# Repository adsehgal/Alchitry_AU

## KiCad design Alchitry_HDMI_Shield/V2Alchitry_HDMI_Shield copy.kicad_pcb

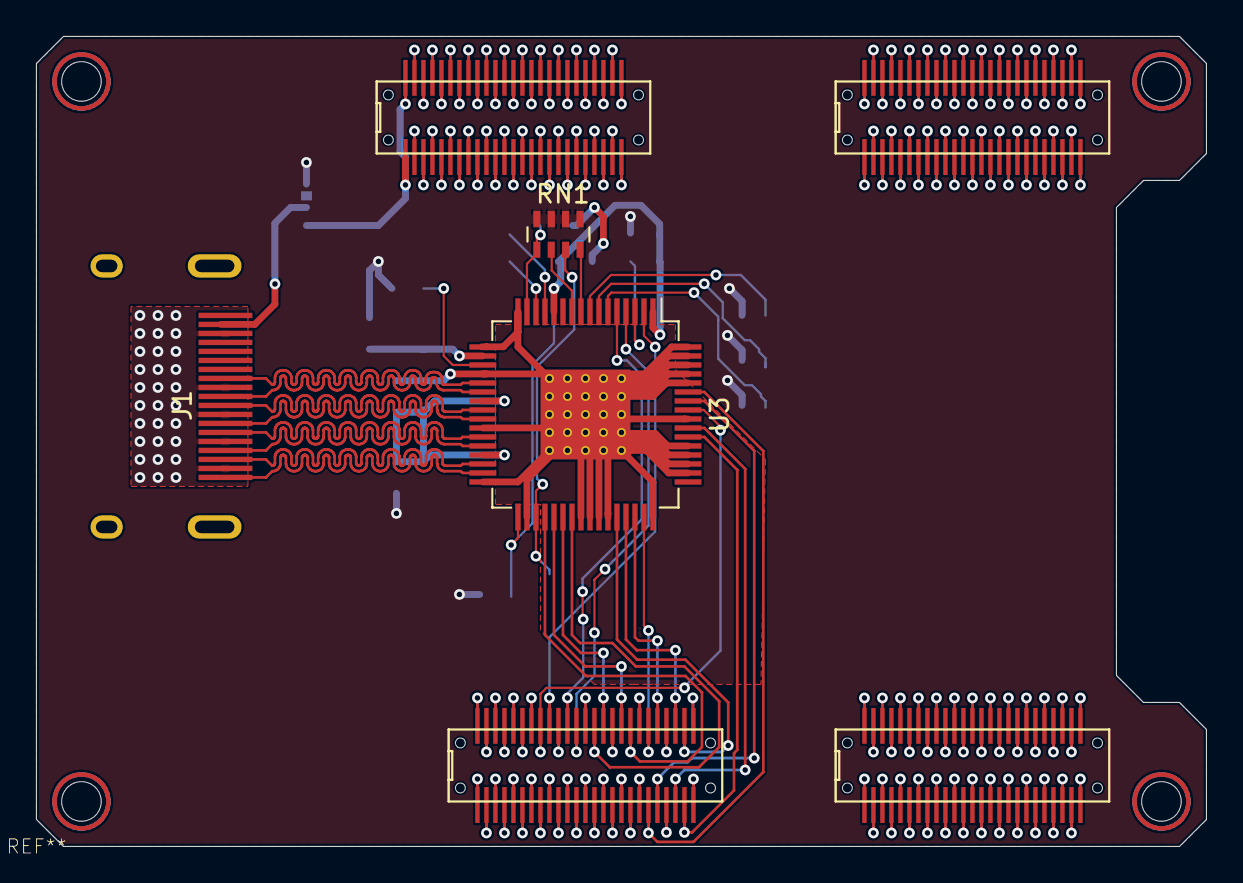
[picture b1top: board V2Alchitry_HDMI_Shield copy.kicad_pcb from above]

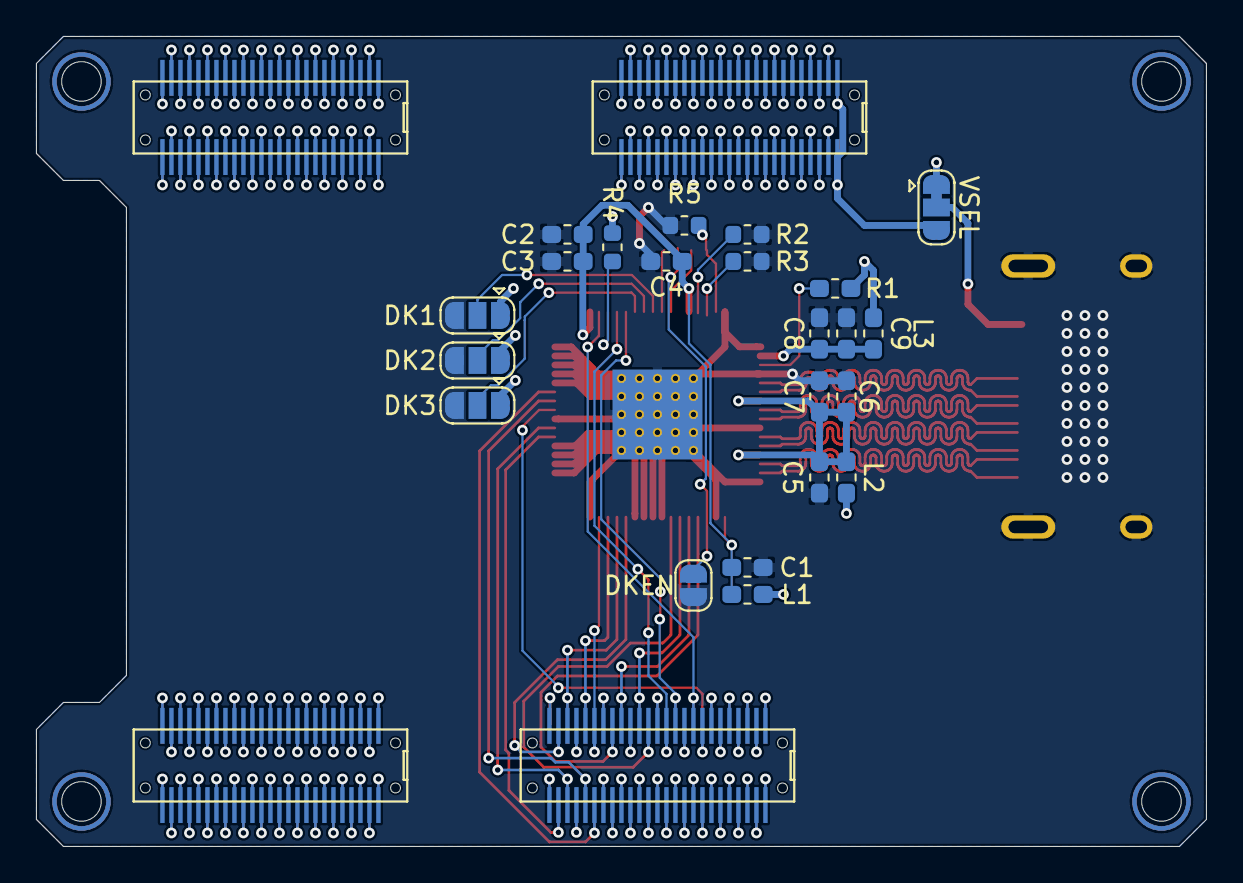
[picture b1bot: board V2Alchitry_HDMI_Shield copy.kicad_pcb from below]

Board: 2 copper layers, 65.0 x 45.0 mm, 25 parts (22 on the bottom side), 25 nets.

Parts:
C1, C2, C3, C5, C6, C8: 100nF; C_0603_1608Metric_Pad1.05x0.95mm_HandSolder
C4, C7, C9: 10µF; C_0603_1608Metric_Pad1.05x0.95mm_HandSolder
DK1: DK1; SolderJumper-3_P1.3mm_Open_RoundedPad1.0x1.5mm
DK2: DK2; SolderJumper-3_P1.3mm_Open_RoundedPad1.0x1.5mm
DK3: DK3; SolderJumper-3_P1.3mm_Open_RoundedPad1.0x1.5mm
DKEN: DKEN; SolderJumper-2_P1.3mm_Open_RoundedPad1.0x1.5mm
J1: HDMI_A_1.4; HDMI
L1, L2, L3: 600; L_0603_1608Metric_Pad1.05x0.95mm_HandSolder
R1: 510; R_0603_1608Metric_Pad1.05x0.95mm_HandSolder
R2, R3: 10K; R_0603_1608Metric
R4: 33K; R_0603_1608Metric
R5: 91K; R_0603_1608Metric
RN1: 10K; R_Array_Concave_4x0603
U3: TFP410; HTQFP-64-1EP_10x10mm_P0.5mm_EP8x8mm_Mask4.4x4.4mm_ThermalVi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
VSEL: V_Sel; SolderJumper-3_P1.3mm_Bridged12_RoundedPad1.0x1.5mm

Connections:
+3V3: DK1.1, DK2.1, DK3.1, L1.1, L2.1, L3.1, R1.1, R4.2, RN1.1, RN1.2, RN1.3, RN1.4, VSEL.1
/HDMI/CK+: J1.10, U3.22
/HDMI/CK-: J1.12, U3.21
/HDMI/D0+: J1.7, U3.25
/HDMI/D0-: J1.9, U3.24
/HDMI/D1+: J1.4, U3.28
/HDMI/D1-: J1.6, U3.27
/HDMI/D2+: J1.1, U3.31
/HDMI/D2-: J1.3, U3.30
/HDMI/DK1: DK1.2, U3.8
/HDMI/DK2: DK2.2, U3.7
/HDMI/DK3: DK3.2, U3.6
/HDMI/ISEL: R2.1, U3.13
GNDREF: C1.2, C2.2, C3.2, C4.2, C5.2, C6.2, C7.2, C8.2, C9.2, DK1.3, DK2.3, DK3.3, DKEN.1, J1.2, J1.5, J1.8, J1.11, J1.17, J1.SH, R2.2, R3.2, R5.2, U3.16, U3.17, U3.20, U3.26, U3.32, U3.34, U3.40, U3.41, U3.42, U3.43, U3.48, U3.50, U3.51, U3.52, U3.53, U3.56, U3.60, U3.61, U3.62, U3.63, U3.64, U3.65
unnamed: C1.1, C2.1, C3.1, C4.1, L1.2, U3.1, U3.12, U3.33
unnamed: C5.1, C6.1, C7.1, L2.2, U3.23, U3.29
unnamed: C8.1, C9.1, L3.2, U3.18
unnamed: J1.18, VSEL.2
unnamed: DKEN.2, RN1.7, U3.35
unnamed: R1.2, U3.19
unnamed: R3.1, U3.14
unnamed: R4.1, U3.3
unnamed: R5.1, RN1.5, U3.15
unnamed: RN1.6, U3.10
unnamed: RN1.8, U3.9

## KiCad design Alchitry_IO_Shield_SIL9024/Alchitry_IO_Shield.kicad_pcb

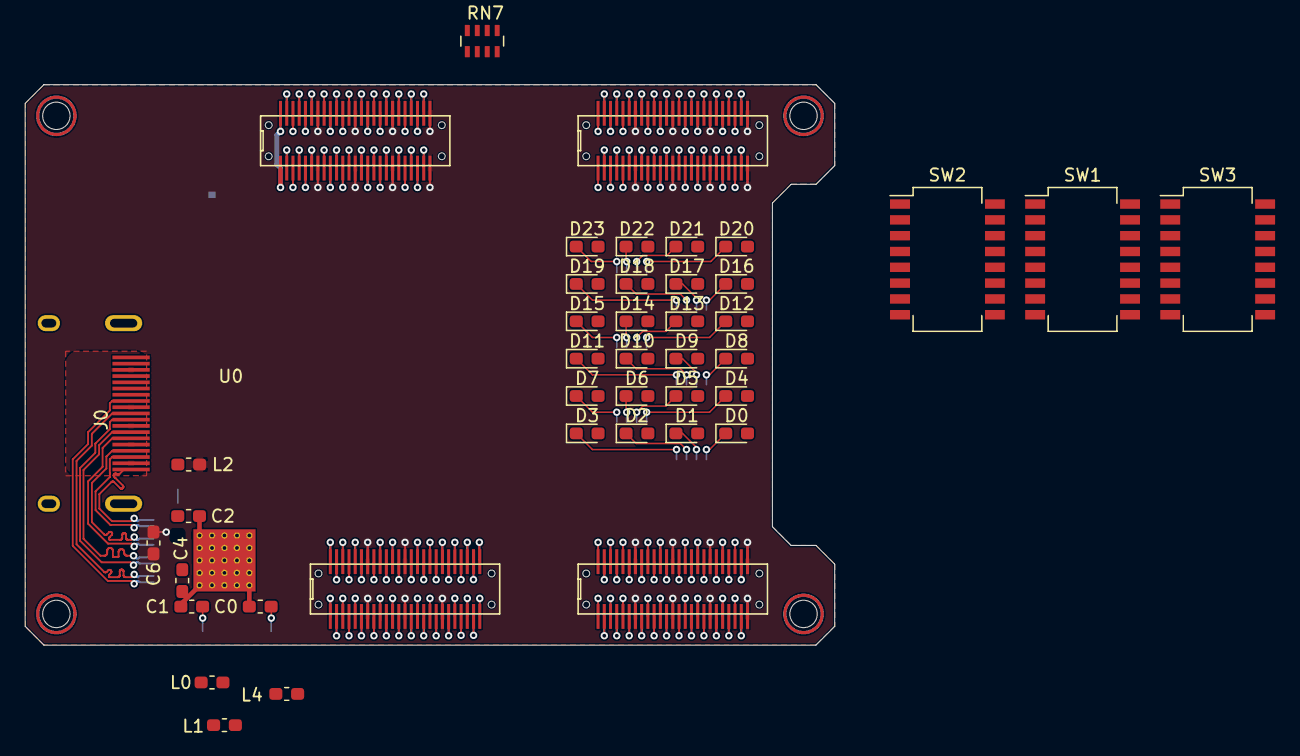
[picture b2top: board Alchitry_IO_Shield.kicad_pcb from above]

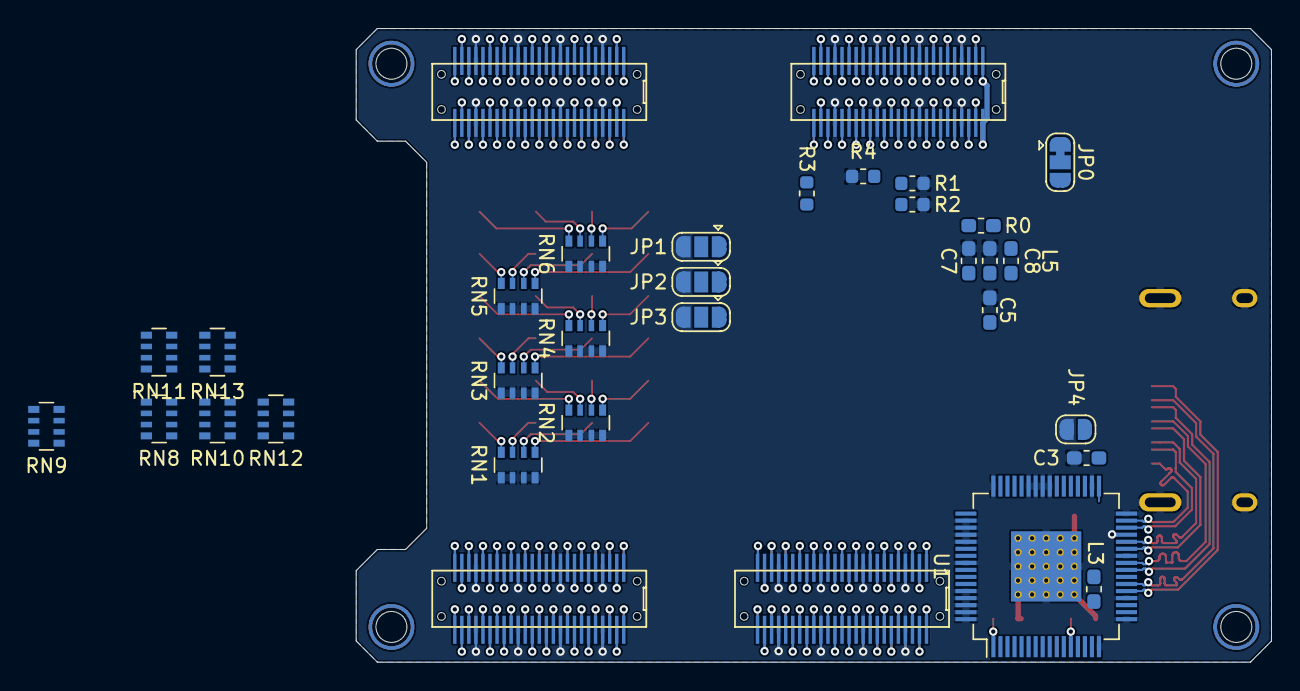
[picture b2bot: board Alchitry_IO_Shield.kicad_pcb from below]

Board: 2 copper layers, 65.0 x 45.0 mm, 68 parts (29 on the bottom side), 214 nets.

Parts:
C0, C1, C2, C4, C5, C7: 100nF; C_0603_1608Metric_Pad1.05x0.95mm_HandSolder
C3, C6, C8: 10µF; C_0603_1608Metric_Pad1.05x0.95mm_HandSolder
D0, D1, D2, D3, D4, D5, D6, D7, D8, D9, D10, D11, D12, D13, D14, D15, D16, D17, D18, D19, D20, D21, D22, D23: LED; LED_0603_1608Metric_Pad1.05x0.95mm_HandSolder
J0: HDMI_A_1.4; HDMI
JP0: V_Sel; SolderJumper-3_P1.3mm_Bridged12_RoundedPad1.0x1.5mm
JP1: DK1; SolderJumper-3_P1.3mm_Open_RoundedPad1.0x1.5mm
JP2: DK2; SolderJumper-3_P1.3mm_Open_RoundedPad1.0x1.5mm
JP3: DK3; SolderJumper-3_P1.3mm_Open_RoundedPad1.0x1.5mm
JP4: DKEN; SolderJumper-2_P1.3mm_Open_RoundedPad1.0x1.5mm
L0, L1, L2, L3, L4, L5: 600; L_0603_1608Metric_Pad1.05x0.95mm_HandSolder
R0: 510; R_0603_1608Metric_Pad1.05x0.95mm_HandSolder
R1, R2: 10K; R_0603_1608Metric
R3: 33K; R_0603_1608Metric
R4: 91K; R_0603_1608Metric
RN1, RN2, RN3, RN4, RN5, RN6, RN8, RN9, RN10, RN11, RN12, RN13: R_Pack04; R_Array_Convex_4x0603
RN7: 10K; R_Array_Concave_4x0603
SW1, SW2, SW3: SW_DIP_x08; SW_DIP_SPSTx08_Slide_Copal_CHS-08B_W7.62mm_P1.27mm
U0: boardmezzanine_new; Alchitry_Top_Bottom
U1: TFP410; HTQFP-64-1EP_10x10mm_P0.5mm_EP8x8mm_Mask4.4x4.4mm_ThermalVi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

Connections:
+3V3: JP0.1, JP1.1, JP2.1, JP3.1, L0.1, L1.1, L2.1, L3.1, L4.1, L5.1, R0.1, R3.2, RN7.1, RN7.2, RN7.3, RN7.4, U0.AB_7, U0.AB_13, U0.AB_19, U0.AB_25, U0.AB_26, U0.AB_32, U0.AB_38, U0.AB_44, U0.AT_7, U0.AT_13, U0.AT_19, U0.AT_25, U0.AT_26, U0.AT_32, U0.AT_38, U0.AT_44, U0.BB_7, U0.BB_13, U0.BB_19, U0.BB_25, U0.BB_26, U0.BB_32, U0.BB_38, U0.BB_44, U0.BT_7, U0.BT_13, U0.BT_19, U0.BT_25, U0.BT_26, U0.BT_32, U0.BT_38, U0.BT_44, U0.CB_7, U0.CB_13, U0.CB_19, U0.CB_38, U0.CB_44, U0.CT_7, U0.CT_13, U0.CT_19, U0.CT_38, U0.CT_44, U0.DB_7, U0.DB_13, U0.DB_19, U0.DB_25, U0.DB_26, U0.DB_32, U0.DB_38, U0.DB_44, U0.DT_7, U0.DT_13, U0.DT_19, U0.DT_25, U0.DT_26, U0.DT_32, U0.DT_38, U0.DT_44
+5V: JP0.3, U0.AB_1, U0.AB_50, U0.AT_1, U0.AT_50
/AN0: U0.AB_43, U0.AT_43
/AN1: U0.AB_42, U0.AT_42
/AN2: U0.AB_8, U0.AT_8
/AN3: U0.AB_9, U0.AT_9
/B0: U0.CB_20, U0.CT_20, U1.59
/B1: U0.CB_21, U0.CT_21, U1.58
/B2: U0.CB_23, U0.CT_23, U1.55
/B3: U0.CB_24, U0.CT_24, U1.54
/BTN0: U0.BB_28, U0.BT_28
/BTN1: U0.BB_27, U0.BT_27
/BTN2: U0.BB_23, U0.BT_23
/BTN3: U0.BB_24, U0.BT_24
/BTN4: U0.CB_49, U0.CT_49
/BTN5: U0.CB_48, U0.CT_48
/BTN6: U0.CB_46, U0.CT_46
/C0: U0.AB_5, U0.AT_5
/C1: U0.AB_6, U0.AT_6
/C2: U0.AB_48, U0.AT_48
/C3: U0.AB_46, U0.AT_46
/C4: U0.AB_45, U0.AT_45
/C5: U0.AB_3, U0.AT_3
/C6: U0.AB_2, U0.AT_2
/CLK: U0.CB_43, U0.CT_43, U1.57
/DE: U0.CB_42, U0.CT_42, U1.2
/DIP0: SW1.8, U0.BB_30, U0.BT_30
/DIP1: SW1.7, U0.BB_31, U0.BT_31
/DIP2: SW1.6, U0.BB_33, U0.BT_33
/DIP3: SW1.5, U0.BB_34, U0.BT_34
/DIP4: SW1.4, U0.BB_36, U0.BT_36
/DIP5: SW1.3, U0.BB_37, U0.BT_37
/DIP6: SW1.2, U0.BB_39, U0.BT_39
/DIP7: SW1.1, U0.BB_40, U0.BT_40
/DIP8: SW2.8, U0.BB_42, U0.BT_42
/DIP9: SW2.7, U0.BB_43, U0.BT_43
/DIP10: SW2.6, U0.BB_45, U0.BT_45
/DIP11: SW2.5, U0.BB_46, U0.BT_46
/DIP12: SW2.4, U0.BB_48, U0.BT_48
/DIP13: SW2.3, U0.BB_49, U0.BT_49
/DIP14: SW2.2, U0.AB_27, U0.AT_27
/DIP15: SW2.1, U0.AB_28, U0.AT_28
/DIP16: SW3.8, U0.AB_30, U0.AT_30
/DIP17: SW3.7, U0.AB_31, U0.AT_31
/DIP18: SW3.6, U0.AB_33, U0.AT_33
/DIP19: SW3.5, U0.AB_34, U0.AT_34
/DIP20: SW3.4, U0.AB_36, U0.AT_36
/DIP21: SW3.3, U0.AB_37, U0.AT_37
/DIP22: SW3.2, U0.AB_39, U0.AT_39
/DIP23: SW3.1, U0.AB_40, U0.AT_40
/DP: U0.AB_49, U0.AT_49
/G0: U0.CB_31, U0.CT_31, U1.47
/G1: U0.CB_30, U0.CT_30, U1.46
/G2: U0.CB_28, U0.CT_28, U1.45
/G3: U0.CB_27, U0.CT_27, U1.44
/HDMI/CK+: J0.10, U1.22
/HDMI/CK-: J0.12, U1.21
/HDMI/D0+: J0.7, U1.25
/HDMI/D0-: J0.9, U1.24
/HDMI/D1+: J0.4, U1.28
/HDMI/D1-: J0.6, U1.27
/HDMI/D2+: J0.1, U1.31
/HDMI/D2-: J0.3, U1.30
/HDMI/DK1: JP1.2, U1.8
/HDMI/DK2: JP2.2, U1.7
/HDMI/DK3: JP3.2, U1.6
/HDMI/ISEL: R1.1, U1.13
/HS: U0.CB_39, U0.CT_39, U1.4
/LED0: D0.2, U0.BB_21, U0.BT_21
/LED1: D1.2, U0.BB_20, U0.BT_20
/LED2: D2.2, U0.BB_18, U0.BT_18
/LED3: D3.2, U0.BB_17, U0.BT_17
/LED4: D4.2, U0.BB_15, U0.BT_15
/LED5: D5.2, U0.BB_14, U0.BT_14
/LED6: D6.2, U0.BB_12, U0.BT_12
/LED7: D7.2, U0.BB_11, U0.BT_11
/LED8: D8.2, U0.BB_9, U0.BT_9
/LED9: D9.2, U0.BB_8, U0.BT_8
/LED10: D10.2, U0.BB_6, U0.BT_6
/LED11: D11.2, U0.BB_5, U0.BT_5
/LED12: D12.2, U0.BB_3, U0.BT_3
/LED13: D13.2, U0.BB_2, U0.BT_2
/LED14: D14.2, U0.AB_24, U0.AT_24
/LED15: D15.2, U0.AB_23, U0.AT_23
/LED16: D16.2, U0.AB_21, U0.AT_21
/LED17: D17.2, U0.AB_20, U0.AT_20
/LED18: D18.2, U0.AB_18, U0.AT_18
/LED19: D19.2, U0.AB_17, U0.AT_17
/LED20: D20.2, U0.AB_15, U0.AT_15
/LED21: D21.2, U0.AB_14, U0.AT_14
/LED22: D22.2, U0.AB_12, U0.AT_12
/LED23: D23.2, U0.AB_11, U0.AT_11
/R0: U0.CB_37, U0.CT_37, U1.39
/R1: U0.CB_36, U0.CT_36, U1.38
/R2: U0.CB_34, U0.CT_34, U1.37
/R3: U0.CB_33, U0.CT_33, U1.36
/VS: U0.CB_40, U0.CT_40, U1.5
GNDREF: C0.2, C1.2, C2.2, C3.2, C4.2, C5.2, C6.2, C7.2, C8.2, J0.2, J0.5, J0.8, J0.11, J0.17, J0.SH, JP1.3, JP2.3, JP3.3, JP4.1, R1.2, R2.2, R4.2, RN1.1, RN1.2, RN1.3, RN1.4, RN2.1, RN2.2, RN2.3, RN2.4, RN3.1, RN3.2, RN3.3, RN3.4, RN4.1, RN4.2, RN4.3, RN4.4, RN5.1, RN5.2, RN5.3, RN5.4, RN6.1, RN6.2, RN6.3, RN6.4, RN8.1, RN8.2, RN8.3, RN8.4, RN9.1, RN9.2, RN9.3, RN9.4, RN10.1, RN10.2, RN10.3, RN10.4, RN11.1, RN11.2, RN11.3, RN11.4, RN12.1, RN12.2, RN12.3, RN12.4, RN13.1, RN13.2, RN13.3, RN13.4, U0.AB_4, U0.AB_10, U0.AB_16, U0.AB_22, U0.AB_29, U0.AB_35, U0.AB_41, U0.AB_47, U0.AT_4, U0.AT_10, U0.AT_16, U0.AT_22, U0.AT_29, U0.AT_35, U0.AT_41, U0.AT_47, U0.BB_4, U0.BB_10, U0.BB_16, U0.BB_22, U0.BB_29, U0.BB_35, U0.BB_41, U0.BB_47, U0.BT_4, U0.BT_10, U0.BT_16, U0.BT_22, U0.BT_29, U0.BT_35, U0.BT_41, U0.BT_47, U0.CB_4, U0.CB_10, U0.CB_16, U0.CB_22, U0.CB_29, U0.CB_35, U0.CB_41, U0.CB_47, U0.CT_4, U0.CT_10, U0.CT_16, U0.CT_22, U0.CT_29, U0.CT_35, U0.CT_41, U0.CT_47, U0.DB_4, U0.DB_10, U0.DB_16, U0.DB_22, U0.DB_29, U0.DB_35, U0.DB_41, U0.DB_47, U0.DT_4, U0.DT_10, U0.DT_16, U0.DT_22, U0.DT_29, U0.DT_35, U0.DT_41, U0.DT_47, U1.16, U1.17, U1.20, U1.26, U1.32, U1.34, U1.40, U1.41, U1.42, U1.43, U1.48, U1.50, U1.51, U1.52, U1.53, U1.56, U1.60, U1.61, U1.62, U1.63, U1.64, U1.65
unnamed: C0.1, L0.2, U1.1
unnamed: C1.1, L1.2, U1.12
unnamed: C2.1, C3.1, L2.2, U1.33
unnamed: C4.1, L3.2, U1.23
unnamed: C5.1, C6.1, L4.2, U1.29
unnamed: C7.1, C8.1, L5.2, U1.18
unnamed: D0.1, RN1.8
unnamed: D1.1, RN1.7
unnamed: D2.1, RN1.6
unnamed: D3.1, RN1.5
unnamed: D4.1, RN2.8
unnamed: D5.1, RN2.7
unnamed: D6.1, RN2.6
unnamed: D7.1, RN2.5
unnamed: D8.1, RN3.8
unnamed: D9.1, RN3.7
unnamed: D10.1, RN3.6
unnamed: D11.1, RN3.5
unnamed: D12.1, RN4.8
unnamed: D13.1, RN4.7
unnamed: D14.1, RN4.6
unnamed: D15.1, RN4.5
unnamed: D16.1, RN5.8
unnamed: D17.1, RN5.7
unnamed: D18.1, RN5.6
unnamed: D19.1, RN5.5
unnamed: D20.1, RN6.8
unnamed: D21.1, RN6.7
unnamed: D22.1, RN6.6
unnamed: D23.1, RN6.5
unnamed: J0.18, JP0.2
unnamed: JP4.2, RN7.7, U1.35
unnamed: R0.2, U1.19
unnamed: R2.1, U1.14
unnamed: R3.1, U1.3
unnamed: R4.1, RN7.5, U1.15
unnamed: RN7.6, U1.10
unnamed: RN7.8, U1.9
unnamed: RN8.5, SW1.12
unnamed: RN8.6, SW1.11
unnamed: RN8.7, SW1.10
unnamed: RN8.8, SW1.9
unnamed: RN9.5, SW1.16
unnamed: RN9.6, SW1.15
unnamed: RN9.7, SW1.14
unnamed: RN9.8, SW1.13
unnamed: RN10.5, SW2.12
unnamed: RN10.6, SW2.11
unnamed: RN10.7, SW2.10
unnamed: RN10.8, SW2.9
unnamed: RN11.5, SW2.16
unnamed: RN11.6, SW2.15
unnamed: RN11.7, SW2.14
unnamed: RN11.8, SW2.13
unnamed: RN12.5, SW3.12
unnamed: RN12.6, SW3.11
unnamed: RN12.7, SW3.10
unnamed: RN12.8, SW3.9
unnamed: RN13.5, SW3.16
unnamed: RN13.6, SW3.15
unnamed: RN13.7, SW3.14
unnamed: RN13.8, SW3.13
unnamed: U0.BB_1, U0.BT_1
unnamed: U0.BB_50, U0.BT_50
unnamed: U0.CB_1, U0.CT_1
unnamed: U0.CB_2, U0.CT_2
unnamed: U0.CB_3, U0.CT_3
unnamed: U0.CB_5, U0.CT_5
unnamed: U0.CB_6, U0.CT_6
unnamed: U0.CB_8, U0.CT_8
unnamed: U0.CB_9, U0.CT_9
unnamed: U0.CB_11, U0.CT_11
unnamed: U0.CB_12, U0.CT_12
unnamed: U0.CB_14, U0.CT_14
unnamed: U0.CB_15, U0.CT_15
unnamed: U0.CB_17, U0.CT_17
unnamed: U0.CB_18, U0.CT_18
unnamed: U0.CB_25, U0.CT_25
unnamed: U0.CB_26, U0.CT_26
unnamed: U0.CB_32, U0.CT_32
unnamed: U0.CB_45, U0.CT_45
unnamed: U0.CB_50, U0.CT_50
unnamed: U0.DB_1, U0.DT_1
unnamed: U0.DB_2, U0.DT_2
unnamed: U0.DB_3, U0.DT_3
unnamed: U0.DB_5, U0.DT_5
unnamed: U0.DB_6, U0.DT_6
unnamed: U0.DB_8, U0.DT_8
unnamed: U0.DB_9, U0.DT_9
unnamed: U0.DB_11, U0.DT_11
unnamed: U0.DB_12, U0.DT_12
unnamed: U0.DB_14, U0.DT_14
unnamed: U0.DB_15, U0.DT_15
unnamed: U0.DB_17, U0.DT_17
unnamed: U0.DB_18, U0.DT_18
unnamed: U0.DB_20, U0.DT_20
unnamed: U0.DB_21, U0.DT_21
unnamed: U0.DB_23, U0.DT_23
unnamed: U0.DB_24, U0.DT_24
unnamed: U0.DB_27, U0.DT_27
unnamed: U0.DB_28, U0.DT_28
unnamed: U0.DB_30, U0.DT_30
unnamed: U0.DB_31, U0.DT_31
unnamed: U0.DB_33, U0.DT_33
unnamed: U0.DB_34, U0.DT_34
unnamed: U0.DB_36, U0.DT_36
unnamed: U0.DB_37, U0.DT_37
unnamed: U0.DB_39, U0.DT_39
unnamed: U0.DB_40, U0.DT_40
unnamed: U0.DB_42, U0.DT_42
unnamed: U0.DB_43, U0.DT_43
unnamed: U0.DB_45, U0.DT_45
unnamed: U0.DB_46, U0.DT_46
unnamed: U0.DB_48, U0.DT_48
unnamed: U0.DB_49, U0.DT_49
unnamed: U0.DB_50, U0.DT_50

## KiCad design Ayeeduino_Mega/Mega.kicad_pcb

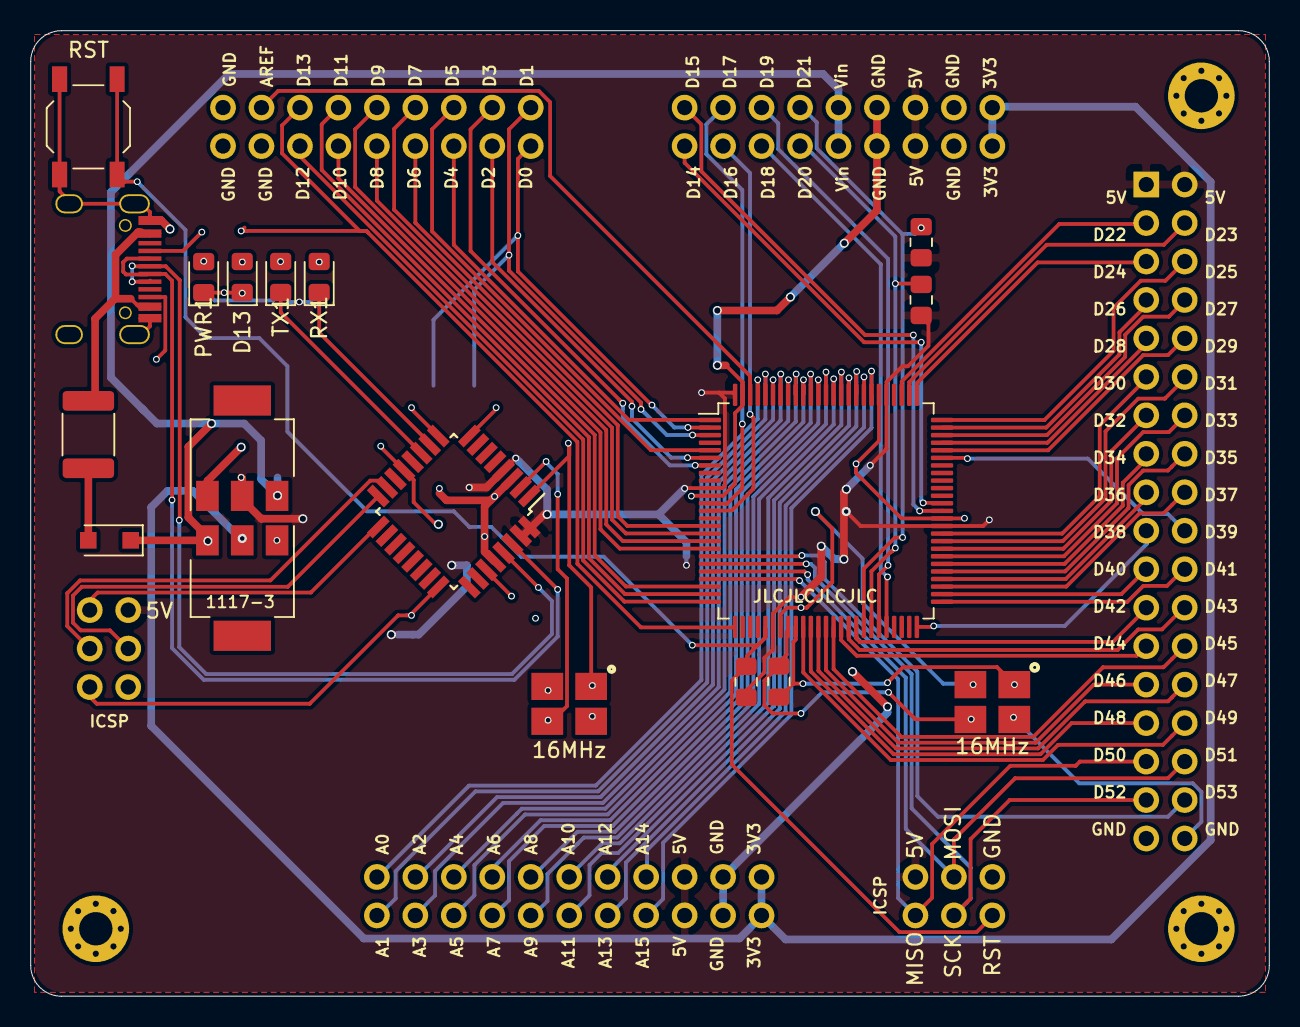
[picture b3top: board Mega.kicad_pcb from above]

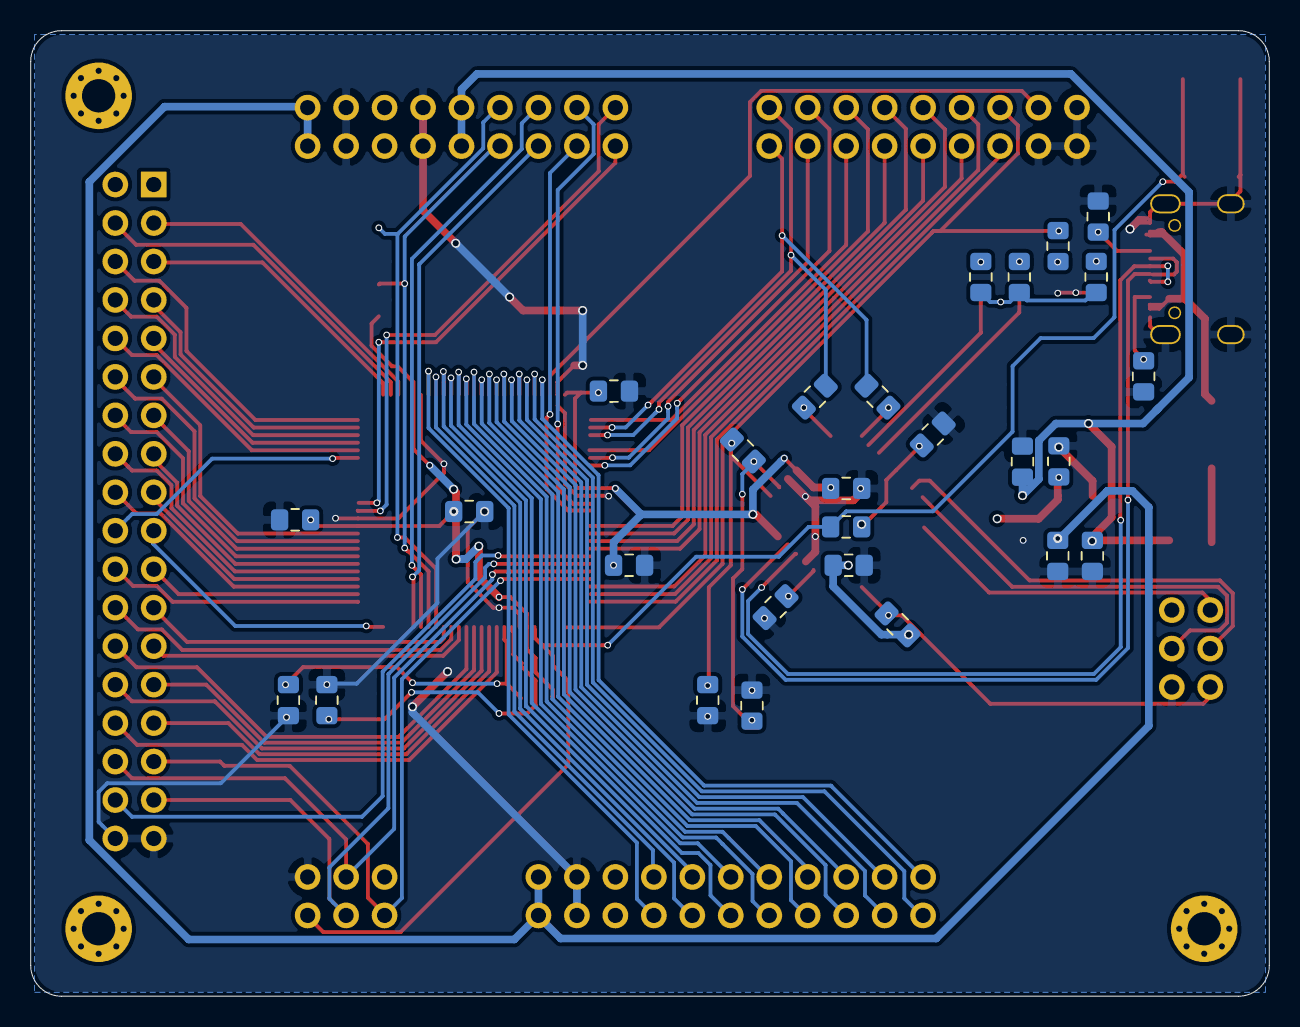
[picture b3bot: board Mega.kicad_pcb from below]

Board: 2 copper layers, 81.8 x 63.8 mm, 54 parts (27 on the bottom side), 100 nets.

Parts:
C1, C2, C3, C4, C5, C6, C12, C13, C14, C15, C16: 100nF; C_0805_2012Metric_Pad1.15x1.40mm_HandSolder
C7, C8, C9, C10: 22pF; C_0805_2012Metric_Pad1.15x1.40mm_HandSolder
C11: 1µF; C_0805_2012Metric_Pad1.15x1.40mm_HandSolder
D1: D; D_SOD-123F
D13: LED; LED_0805_2012Metric_Pad1.15x1.40mm_HandSolder
F1: Fuse; Fuse_1812_4532Metric_Pad1.30x3.40mm_HandSolder
H1, H3, H4: MountingHole; MountingHole_2.2mm_M2_Pad_Via
J1: D14-21 [COMMS]; PinHeader_2x09_P2.54mm_Vertical
J2: D22-53[SERIAL]; PinHeader_2x18_P2.54mm_Vertical
J3: D0-13 [~PWM]; PinHeader_2x09_P2.54mm_Vertical
J4, J6: ICSP; PinHeader_2x03_P2.54mm_Vertical
J5: A0-15; PinHeader_2x11_P2.54mm_Vertical
P1: USB_C_Plug; USB C C167321
PWR1: LED; LED_0805_2012Metric_Pad1.15x1.40mm_HandSolder
R1, R3, R6, R7, R8, R9: 1KΩ; R_0805_2012Metric_Pad1.15x1.40mm_HandSolder
R2, R5: 1MΩ; R_0805_2012Metric_Pad1.15x1.40mm_HandSolder
R4: 10KΩ; R_0805_2012Metric_Pad1.15x1.40mm_HandSolder
R10, R11: 5.1KΩ; R_0805_2012Metric_Pad1.15x1.40mm_HandSolder
R12, R13, R14: R_Small_US; R_0805_2012Metric_Pad1.15x1.40mm_HandSolder
R15: 330Ω; R_0805_2012Metric_Pad1.15x1.40mm_HandSolder
RX1: LED; LED_0805_2012Metric_Pad1.15x1.40mm_HandSolder
SW1: RST; SW_SPST_TL3342
TX1: LED; LED_0805_2012Metric_Pad1.15x1.40mm_HandSolder
U1: 1115-5; SOT-223
U2: 1117-3; SOT-223
U3: ATmega16U2-AU; TQFP-32_7x7mm_P0.8mm
U4: ATmega2560-16AU; TQFP-100_14x14mm_P0.5mm
Y1, Y2: 16MHz; Crystal_SMD_3225-4Pin_3.2x2.5mm_HandSoldering

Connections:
+3V3: C4.2, J1.9, J1.10, J5.21, J5.22, U2.2
+5V: C2.2, C5.2, C6.2, C13.2, C14.2, C15.2, C16.2, J1.7, J1.12, J2.1, J2.2, J4.2, J5.17, J5.18, J6.2, R1.2, R4.2, R7.2, R8.2, R12.1, R14.1, R15.1, U1.2, U3.4, U3.31, U3.32, U4.10, U4.31, U4.61, U4.80, U4.100
+VSW: C1.1, C3.1, D1.1, J1.5, J1.14, U1.3, U2.3
/D+: P1.A6, P1.B6, U3.29
/D-: P1.A7, P1.B7, U3.30
/MISO_1: J6.1, U3.17
/MOSI_1: J6.4, U3.16
/RST_1: J6.5, R4.1, U3.24
/SCK_1: J6.3, U3.15
A0: J5.2, U4.97
A1: J5.1, U4.96
A2: J5.4, U4.95
A3: J5.3, U4.94
A4: J5.6, U4.93
A5: J5.5, U4.92
A6: J5.8, U4.91
A7: J5.7, U4.90
A8: J5.10, U4.89
A9: J5.9, U4.88
A10: J5.12, U4.87
A11: J5.11, U4.86
A12: J5.14, U4.85
A13: J5.13, U4.84
A14: J5.16, U4.83
A15: J5.15, U4.82
AREF: J3.8, U4.98
D0: J3.18, R3.1, U4.2
D1: J3.1, R6.1, U4.3
D2: J3.17, U4.6
D3: J3.2, U4.7
D4: J3.16, U4.1
D5: J3.3, U4.5
D6: J3.15, U4.15
D7: J3.4, U4.16
D8: J3.14, U4.17
D9: J3.5, U4.18
D10: J3.13, U4.23
D11: J3.6, U4.24
D12: J3.12, U4.25
D13: J3.7, R13.1, U4.26
D14: J1.1, U4.64
D15: J1.18, U4.63
D16: J1.2, U4.13
D17: J1.17, U4.12
D18: J1.3, U4.46
D19: J1.16, U4.45
D20: J1.4, R8.1, U4.44
D21: J1.15, R7.1, U4.43
D22: J2.3, U4.78
D23: J2.4, U4.77
D24: J2.5, U4.76
D25: J2.6, U4.75
D26: J2.7, U4.74
D27: J2.8, U4.73
D28: J2.9, U4.72
D29: J2.10, U4.71
D30: J2.11, U4.60
D31: J2.12, U4.59
D32: J2.13, U4.58
D33: J2.14, U4.57
D34: J2.15, U4.56
D35: J2.16, U4.55
D36: J2.17, U4.54
D37: J2.18, U4.53
D38: J2.19, U4.50
D39: J2.20, U4.70
D40: J2.21, U4.52
D41: J2.22, U4.51
D42: J2.23, U4.42
D43: J2.24, U4.41
D44: J2.25, U4.40
D45: J2.26, U4.39
D46: J2.27, U4.38
D47: J2.28, U4.37
D48: J2.29, U4.36
D49: J2.30, U4.35
D50_MISO: J2.31, J4.1, U4.22
D51_MOSI: J2.32, J4.4, U4.21
D52_SCK: J2.33, J4.3, U4.20
D53_SS: J2.34, U4.19
GNDREF: C1.2, C2.1, C3.2, C4.1, C5.1, C6.1, C7.2, C8.2, C9.2, C10.2, C11.1, C13.1, C14.1, C15.1, C16.1, D13.1, J1.6, J1.8, J1.11, J1.13, J2.35, J2.36, J3.9, J3.10, J3.11, J4.6, J5.19, J5.20, J6.6, P1.A1, P1.A12, P1.B1, P1.B12, P1.S1, PWR1.1, R9.1, R10.1, R11.1, SW1.2, U1.1, U2.1, U3.3, U3.28, U4.11, U4.32, U4.62, U4.81, U4.99, Y1.2, Y1.4, Y2.2, Y2.4
unnamed: C7.1, R5.2, U3.1, Y2.1
unnamed: C8.1, R5.1, U3.2, Y2.3
unnamed: C9.1, R2.2, U4.34, Y1.1
unnamed: C10.1, R2.1, U4.33, Y1.3
unnamed: C11.2, U3.27
unnamed: C12.2, R9.2, U3.13
unnamed: D1.2, F1.2
unnamed: D13.2, R13.2
unnamed: F1.1, P1.A4, P1.A9, P1.B4, P1.B9
unnamed: P1.A5, R10.2
unnamed: P1.B5, R11.2
unnamed: PWR1.2, R12.2
unnamed: R14.2, TX1.2
unnamed: R15.2, RX1.2
RST: C12.1, J4.5, R1.1, SW1.1, U4.30
RX: R3.2, U3.9
RXL: RX1.1, U3.10
TX: R6.2, U3.8
TXL: TX1.1, U3.11

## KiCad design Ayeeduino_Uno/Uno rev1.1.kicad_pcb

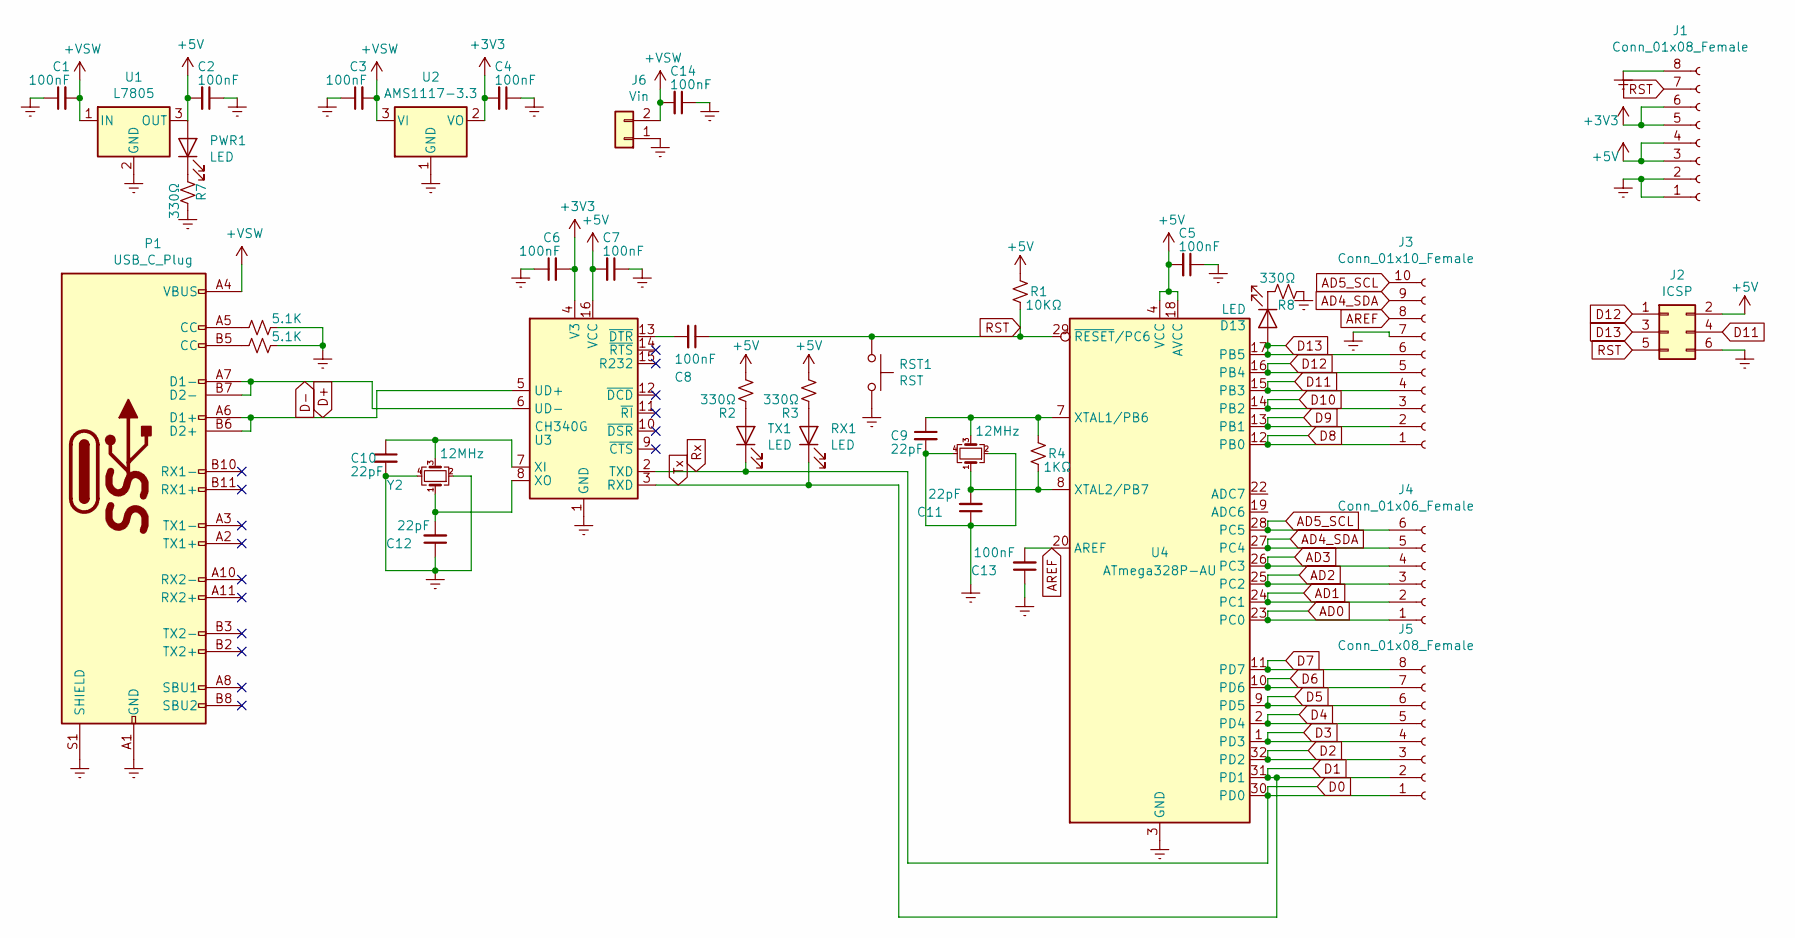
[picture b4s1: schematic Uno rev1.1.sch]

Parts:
C1, C2, C3, C4, C5, C6, C7, C8, C13, C14: 100nF; C_0805_2012Metric_Pad1.15x1.40mm_HandSolder
C9, C10, C11, C12: 22pF; C_0805_2012Metric_Pad1.15x1.40mm_HandSolder
D13: LED; LED_0805_2012Metric_Pad1.15x1.40mm_HandSolder
J1, J5: Conn_01x08_Female; PinHeader_1x08_P2.54mm_Vertical
J2: ICSP; PinHeader_2x03_P2.54mm_Vertical
J3: Conn_01x10_Female; PinHeader_1x10_P2.54mm_Vertical
J4: Conn_01x06_Female; PinHeader_1x06_P2.54mm_Vertical
J6: Vin; PinSocket_1x02_P2.54mm_Vertical
P1: USB_C_Plug; USB C C167321
PWR1: LED; LED_0805_2012Metric_Pad1.15x1.40mm_HandSolder
R1: 10KΩ; R_0805_2012Metric_Pad1.15x1.40mm_HandSolder
R2, R3, R7, R8: 330Ω; R_0805_2012Metric_Pad1.15x1.40mm_HandSolder
R4: 1KΩ; R_0805_2012Metric_Pad1.15x1.40mm_HandSolder
R5, R6: 5.1K; R_0805_2012Metric_Pad1.15x1.40mm_HandSolder
RST1: RST; SW_SPST_TL3342
RX1: LED; LED_0805_2012Metric_Pad1.15x1.40mm_HandSolder
TX1: LED; LED_0805_2012Metric_Pad1.15x1.40mm_HandSolder
U1: L7805; SOT-89-3_Handsoldering
U2: AMS1117-3.3; SOT-223-3_TabPin2
U3: CH340G; SOIC-16_3.9x9.9mm_P1.27mm
U4: ATmega328P-AU; TQFP-32_7x7mm_P0.8mm
Y1, Y2: 12MHz; Crystal_SMD_3225-4Pin_3.2x2.5mm_HandSoldering

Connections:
+3V3: C4.2, C6.2, J1.5, J1.6, U2.2 (VO), U3.4 (V3)
+5V: C2.2, C5.2, C7.2, J1.3, J1.4, J2.2, PWR1.2 (A), R1.1, R2.2, R3.2, U1.3 (OUT), U3.16 (VCC), U4.4 (VCC), U4.6 (VCC), U4.18 (AVCC)
+VSW: C1.2, C3.2, C14.2, J6.2, P1.A4 (VBUS), P1.A9 (VBUS), P1.B4 (VBUS), P1.B9 (VBUS), U1.1 (IN), U2.3 (VI)
AD0: J4.1, U4.23 (PC0)
AD1: J4.2, U4.24 (PC1)
AD2: J4.3, U4.25 (PC2)
AD3: J4.4, U4.26 (PC3)
AD4_SDA: J3.9, J4.5, U4.27 (PC4)
AD5_SCL: J3.10, J4.6, U4.28 (PC5)
AREF: C13.2, J3.8, U4.20 (AREF)
D0: J5.1, TX1.1 (K), U3.2 (TXD), U4.30 (PD0)
D1: J5.2, RX1.1 (K), U3.3 (RXD), U4.31 (PD1)
D2: J5.3, U4.32 (PD2)
D3: J5.4, U4.1 (PD3)
D4: J5.5, U4.2 (PD4)
D5: J5.6, U4.9 (PD5)
D6: J5.7, U4.10 (PD6)
D7: J5.8, U4.11 (PD7)
D8: J3.1, U4.12 (PB0)
D9: J3.2, U4.13 (PB1)
D10: J3.3, U4.14 (PB2)
D11: J2.4, J3.4, U4.15 (PB3)
D12: J2.1, J3.5, U4.16 (PB4)
D13: D13.2 (A), J2.3, J3.6, U4.17 (PB5)
D+: P1.A6 (D1+), P1.B6 (D2+), U3.5 (UD+)
D-: P1.A7 (D1-), P1.B7 (D2-), U3.6 (UD-)
GNDREF: C1.1, C2.1, C3.1, C4.1, C5.1, C6.1, C7.1, C9.2, C10.2, C11.1, C12.1, C13.1, C14.1, J1.1, J1.2, J1.8, J2.6, J3.7, J6.1, P1.A1 (GND), P1.A12 (GND), P1.B1 (GND), P1.B12 (GND), P1.S1 (SHIELD), R5.1, R6.1, R7.2, R8.1, RST1.2, U1.2 (GND), U2.1 (GND), U3.1 (GND), U4.3 (GND), U4.5 (GND), U4.21 (GND), Y1.2, Y1.4, Y2.2, Y2.4; also elsewhere on the board
unnamed: C8.2, U3.13 (~DTR)
unnamed 28: C9.1, R4.1, U4.7 (XTAL1/PB6), Y1.3; also elsewhere on the board
unnamed: C10.1, U3.7 (XI), Y2.3
unnamed 30: C11.2, R4.2, U4.8 (XTAL2/PB7), Y1.1; also elsewhere on the board
unnamed: C12.2, U3.8 (XO), Y2.1
unnamed: D13.1 (K), R8.2
unnamed: P1.A5 (CC), R5.2
unnamed: P1.B5 (CC), R6.2
unnamed: PWR1.1 (K), R7.1
unnamed: R2.1, TX1.2 (A)
unnamed: R3.1, RX1.2 (A)
RST: C8.1, J1.7, J2.5, R1.2, RST1.1, U4.29 (~RESET~/PC6)

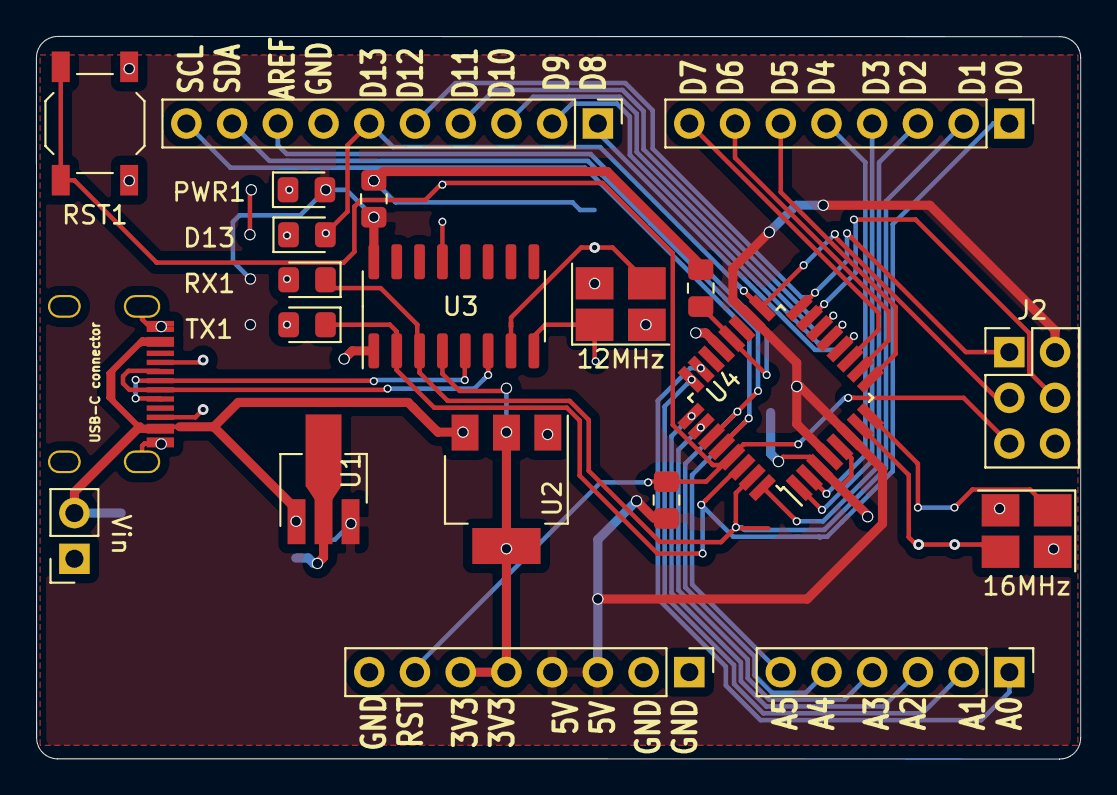
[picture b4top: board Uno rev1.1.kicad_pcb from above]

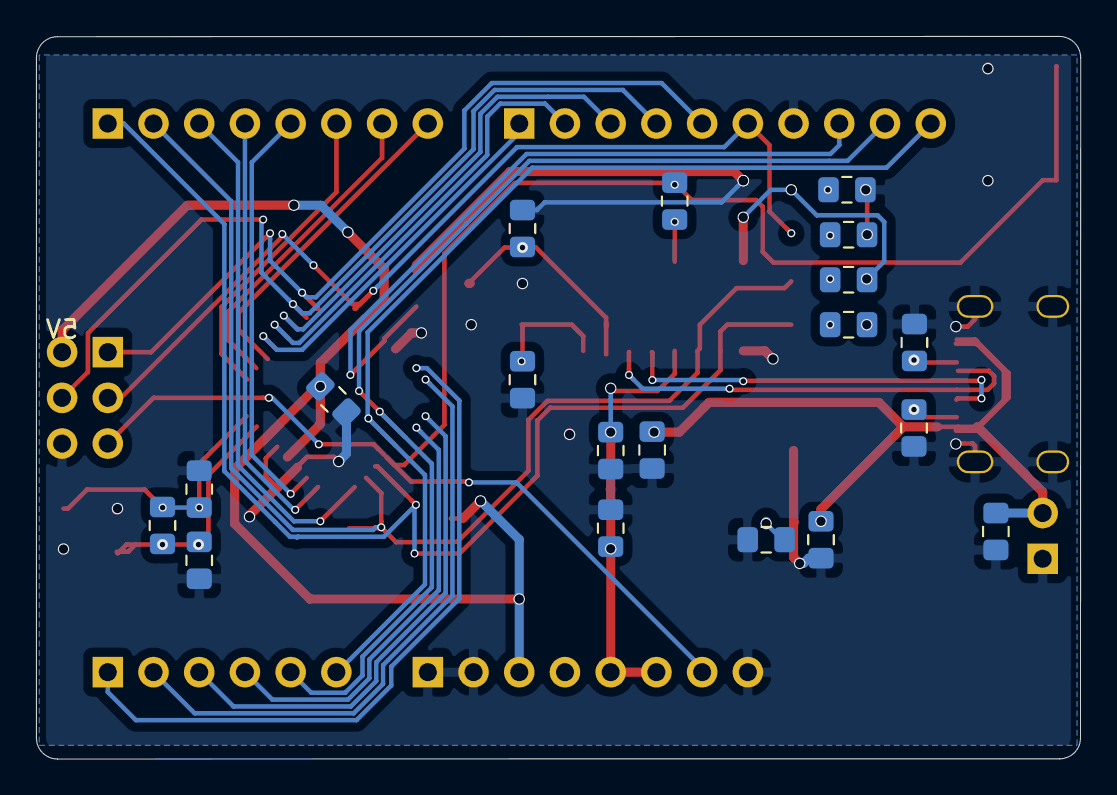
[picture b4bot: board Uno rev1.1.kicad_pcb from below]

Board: 2 copper layers, 58.0 x 40.1 mm, 40 parts (19 on the bottom side), 39 nets.

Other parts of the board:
16MHz: 12MHz; Crystal_SMD_3225-4Pin_3.2x2.5mm_HandSoldering

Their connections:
GNDREF: 16MHz.2, 16MHz.4; also elsewhere on the board
unnamed 28: 16MHz.3; also elsewhere on the board
unnamed 30: 16MHz.1; also elsewhere on the board
